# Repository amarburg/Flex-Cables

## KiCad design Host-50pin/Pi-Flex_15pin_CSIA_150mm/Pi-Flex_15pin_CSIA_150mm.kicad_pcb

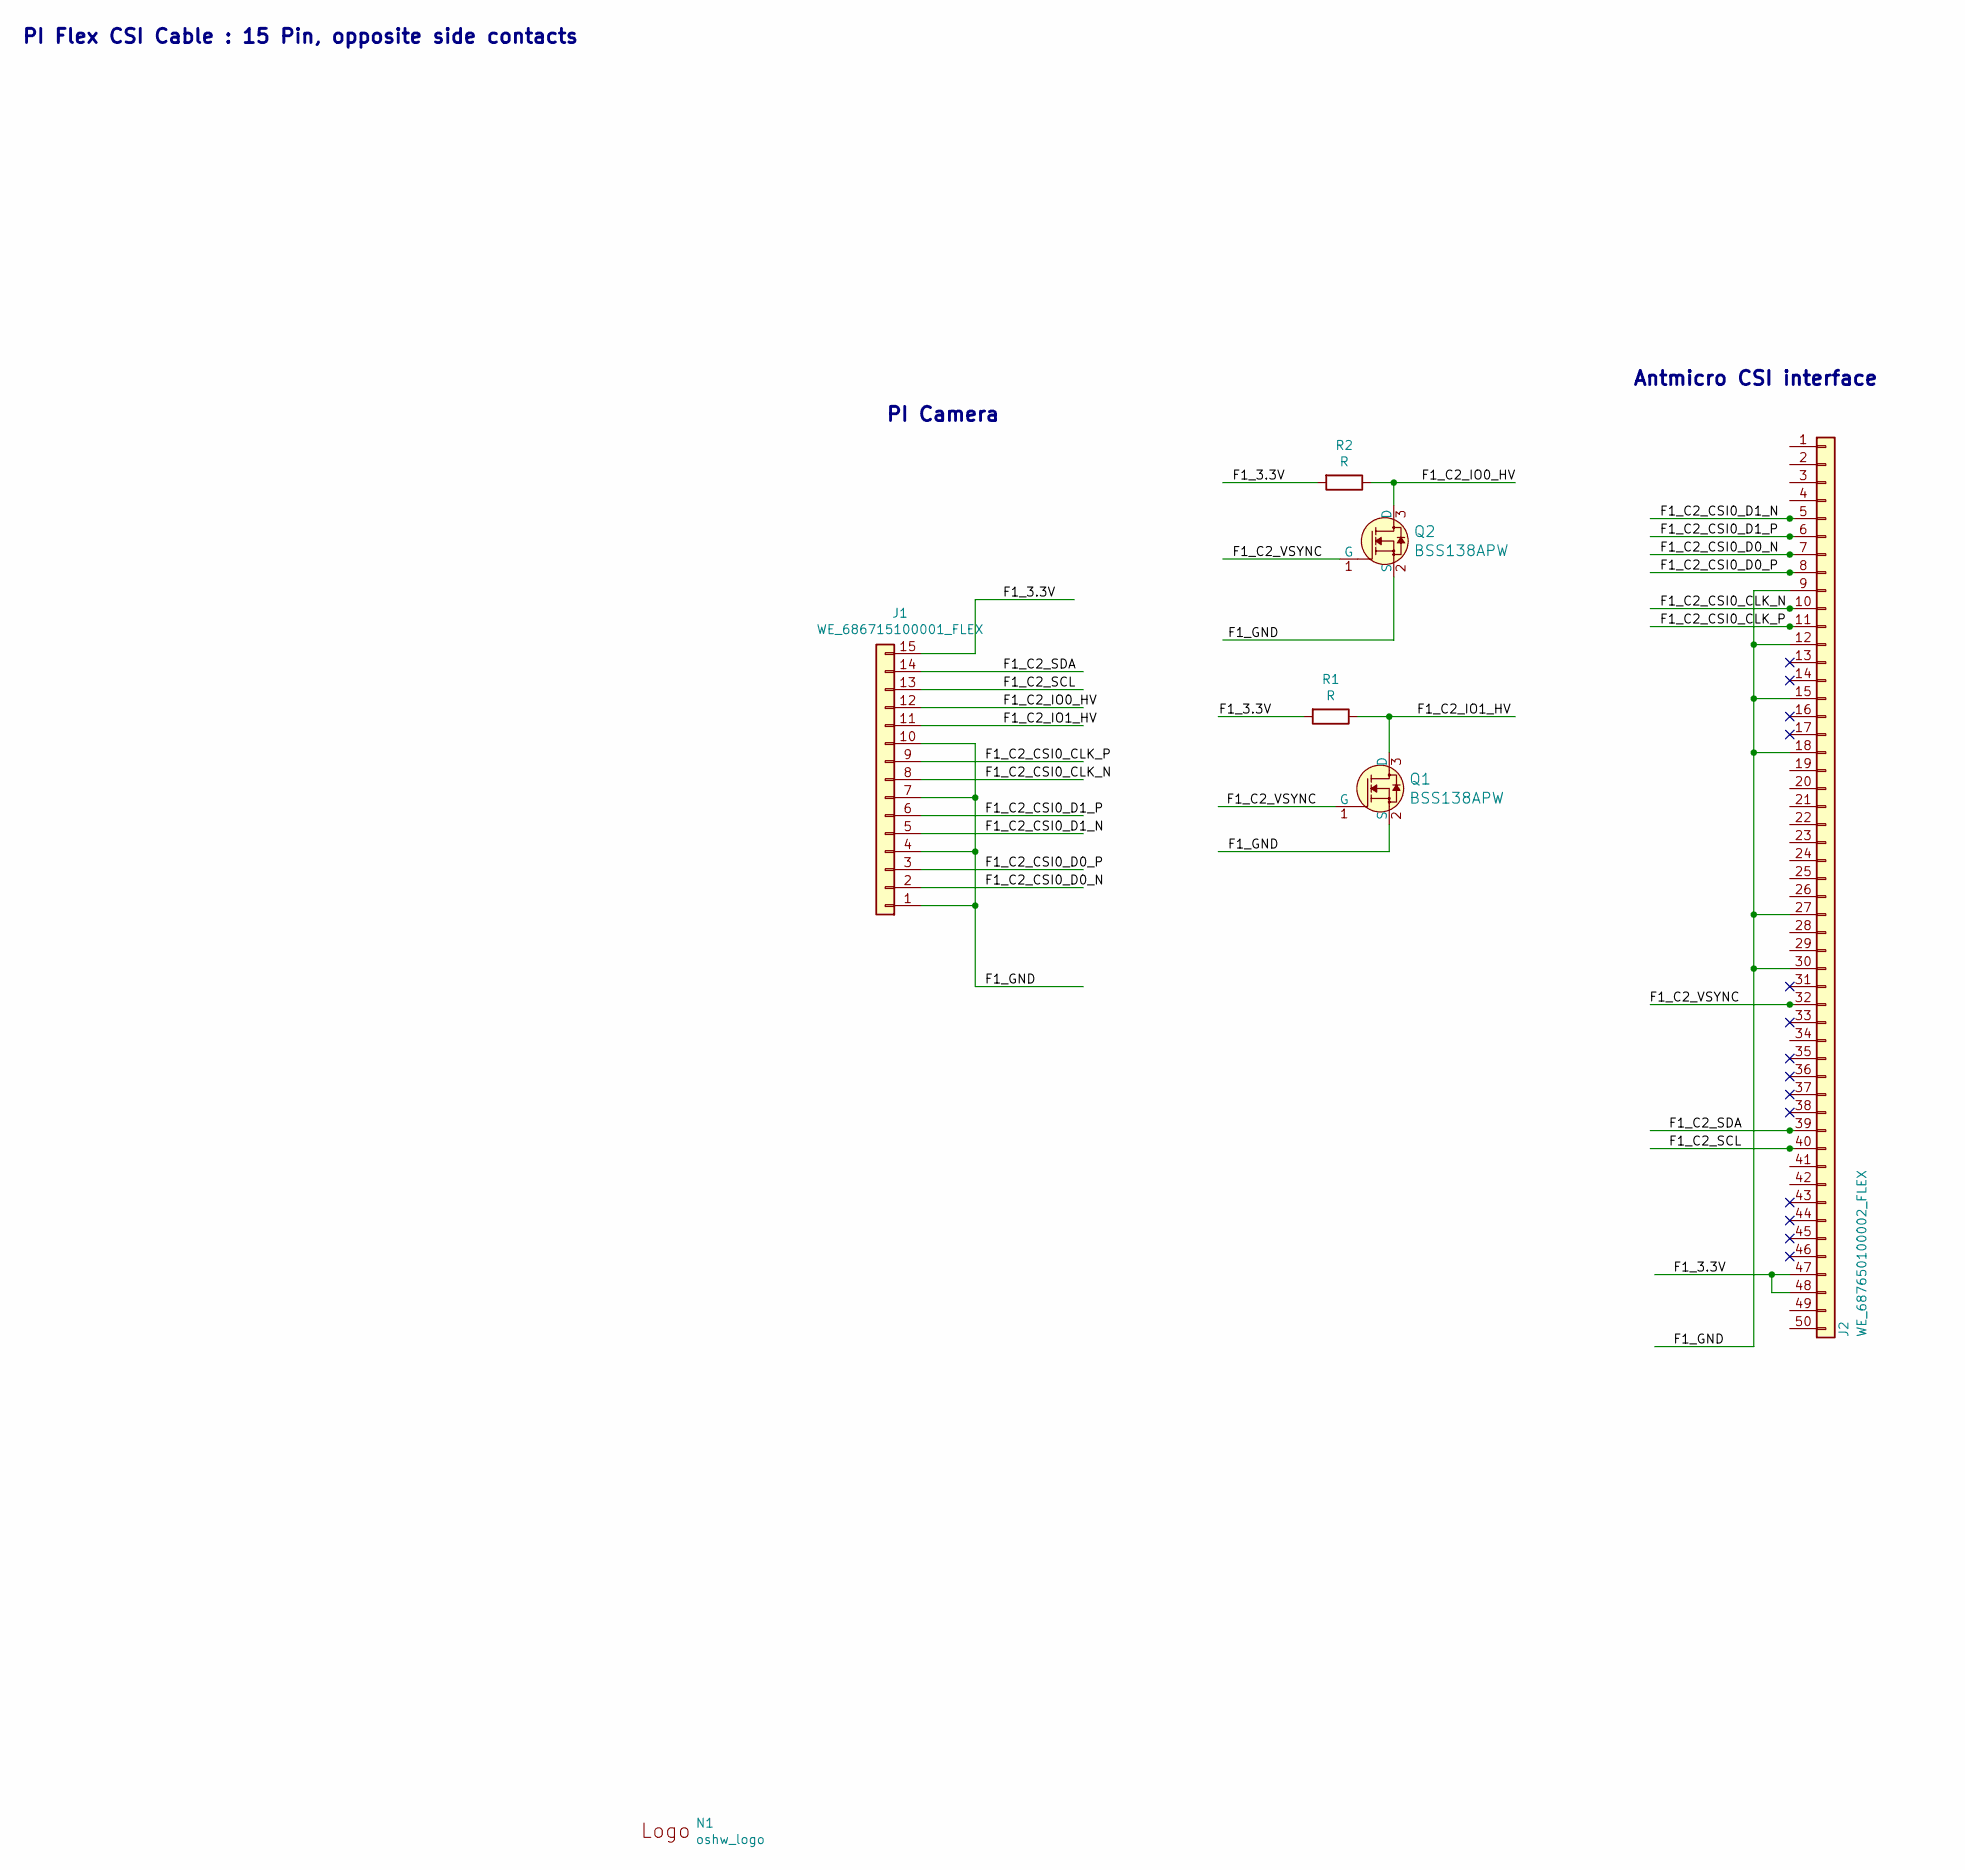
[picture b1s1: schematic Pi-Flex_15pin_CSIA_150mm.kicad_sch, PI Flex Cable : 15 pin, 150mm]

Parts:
J1: WE_686715100001_FLEX; WE_ 686715100001_FLEX; MPN 686715100001
J2: WE_687650100002_FLEX; MPN 687650100002
N1: oshw_logo; oshw-logo
Q1, Q2: BSS138APW; SC70-3; MPN BSS138PW
R1, R2: R; R_0402_1005Metric

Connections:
/F1_3.3V: J1.15, J2.47, J2.48, R1.2, R2.2
/F1_C2_CSI0_CLK_N: J1.8, J2.10
/F1_C2_CSI0_CLK_P: J1.9, J2.11
/F1_C2_CSI0_D0_N: J1.2, J2.7
/F1_C2_CSI0_D0_P: J1.3, J2.8
/F1_C2_CSI0_D1_N: J1.5, J2.5
/F1_C2_CSI0_D1_P: J1.6, J2.6
/F1_C2_IO0_HV: J1.12, Q2.3 (D), R2.1
/F1_C2_IO1_HV: J1.11, Q1.3 (D), R1.1
/F1_C2_SCL: J1.13, J2.40
/F1_C2_SDA: J1.14, J2.39
/F1_C2_VSYNC: J2.32, Q1.1 (G), Q2.1 (G)
/F1_GND: J1.1, J1.4, J1.7, J1.10, J2.9, J2.12, J2.15, J2.18, J2.27, J2.30, Q1.2 (S), Q2.2 (S)

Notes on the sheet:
PI Flex CSI Cable : 15 Pin, opposite side contacts
PI Camera
Antmicro CSI interface

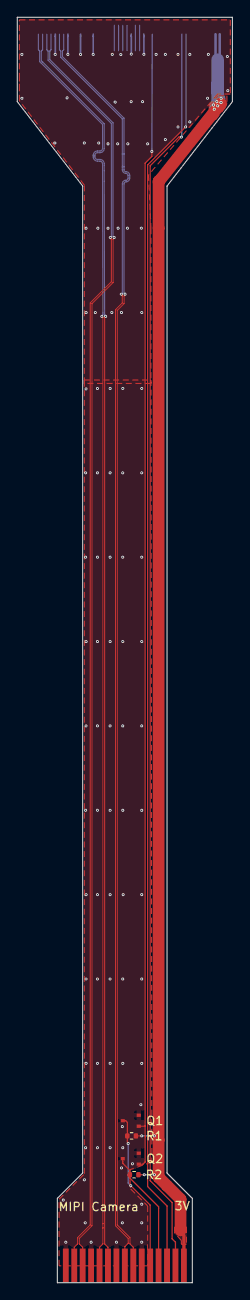
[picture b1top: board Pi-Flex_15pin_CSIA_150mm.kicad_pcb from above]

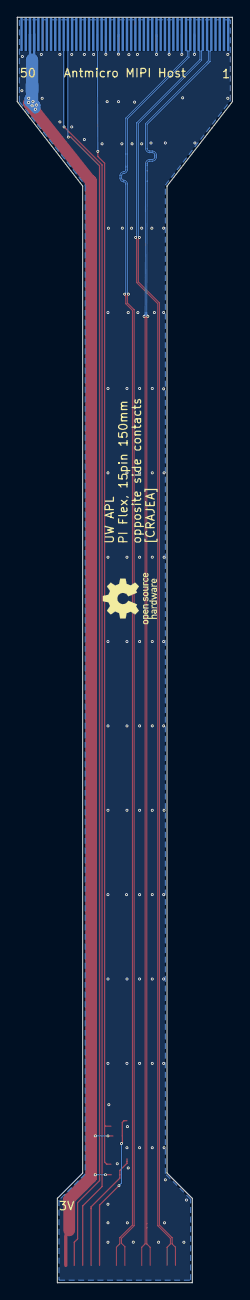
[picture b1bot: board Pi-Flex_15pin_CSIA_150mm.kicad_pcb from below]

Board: 2 copper layers, 25.5 x 150.0 mm, 7 parts (2 on the bottom side), 13 nets.
